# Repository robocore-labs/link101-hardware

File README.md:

# link101 Hardware

link101 is a multi-protocol USB interface board. One Type-C cable gives you CAN-FD, RS485, Dynamixel, Feetech, UART, I2C, and MIT Cheetah-protocol ports, all as stable Linux devices.

## Architecture

The LINK101 system consists of two boards:

- **link101** — The core module. RP2350-based controller in a 39.2×36.6mm form factor with 2× 1×15 pin headers.
- **link101_carrier** — The breakout carrier board. Exposes every bus as physical connectors, adds onboard sensors, neopixel indicators, and a 5V buck regulator.

## Boards

### link101 (Module)

The brains of the system. A Raspberry Pi RP2354A (dual Cortex-M33 at 150 MHz, 520 KB SRAM, 2 MB flash) with onboard peripherals:

| Feature | Detail |
|---|---|
| **USB** | USB Type-C composite device (CDC serial, SocketCAN, debug) |
| **CAN** | MCP2518FD CAN-FD controller + SN65HVD230 transceiver |
| **RS485** | SP3485EN half-duplex transceiver with DE control |
| **GPIO** | 7× GPIO, 4× ADC exposed via pin headers |
| **I2C** | Hardware I2C bus (SCL/SDA) |
| **SPI** | Hardware SPI (MOSI/MISO/SCK) |
| **UART** | 2× full-duplex UART (UART0, UART1) |
| **NeoPixel** | WS2812B-compatible output |
| **Power** | VBUS input, onboard 3.3V LDO (AP2112K-3.3), 1.1V core supply |
| **Protection** | ESD protection on CAN (PESD1CAN), USB (USBLC6-2SC6), and RS485 (PRTR5V0U2X) |
| **Debug** | SWD header, USB boot select |

**Files:** `link101.kicad_pro` (project), `link101.kicad_sch` (schematic), `link101.kicad_pcb` (layout), `link101_Module.kicad_sym` (symbol), `link101_Module.kicad_mod` (footprint)

### link101_carrier (Carrier Board)

Breaks out every signal from the module into real-world connectors, adds sensors, neopixel status LEDs, and power regulation:

| Section | Details |
|---|---|
| **Power** | XT30 input → LMR16006 5V buck regulator → SS54 reverse protection → servo power rail |
| **CAN-FD** | Screw terminals, MCP2518FD via module SPI |
| **RS485** | Screw terminals, hardware UART with DE pin |
| **UART0** | 5V-level full-duplex serial (XH2.54 connector) |
| **UART1** | 3.3V-level full-duplex serial (2.54mm pin header) |
| **Half-Duplex UART** | Feetech SCS/STS, Dynamixel Protocol 1.0/2.0, FashionStar bus servos (XH2.54 + Dynamixel connectors) |
| **I2C** | Qwiic/STEMMA QT connector (JST-GH 4-pin) |
| **SPI** | 2.54mm pin header |
| **MIT Cheetah** | XT30(2+2) connector for Damiao, CubeMars, Unitree, MyActuator |
| **ODrive** | JST-GH 4-pin connector |
| **IMU** | Onboard LSM6DSOX 6-axis IMU + MMC5983MA magnetometer via SPI |
| **NeoPixels** | WS2812B ×4 — one per bus (CAN, RS485, serial, servo) |
| **GPIO/ADC** | 7× GPIO + 4× ADC breakout pin headers |

**Files:** `link101_carrier.kicad_pro` (project), `link101_carrier.kicad_sch` (schematic), `link101_carrier.kicad_pcb` (layout)

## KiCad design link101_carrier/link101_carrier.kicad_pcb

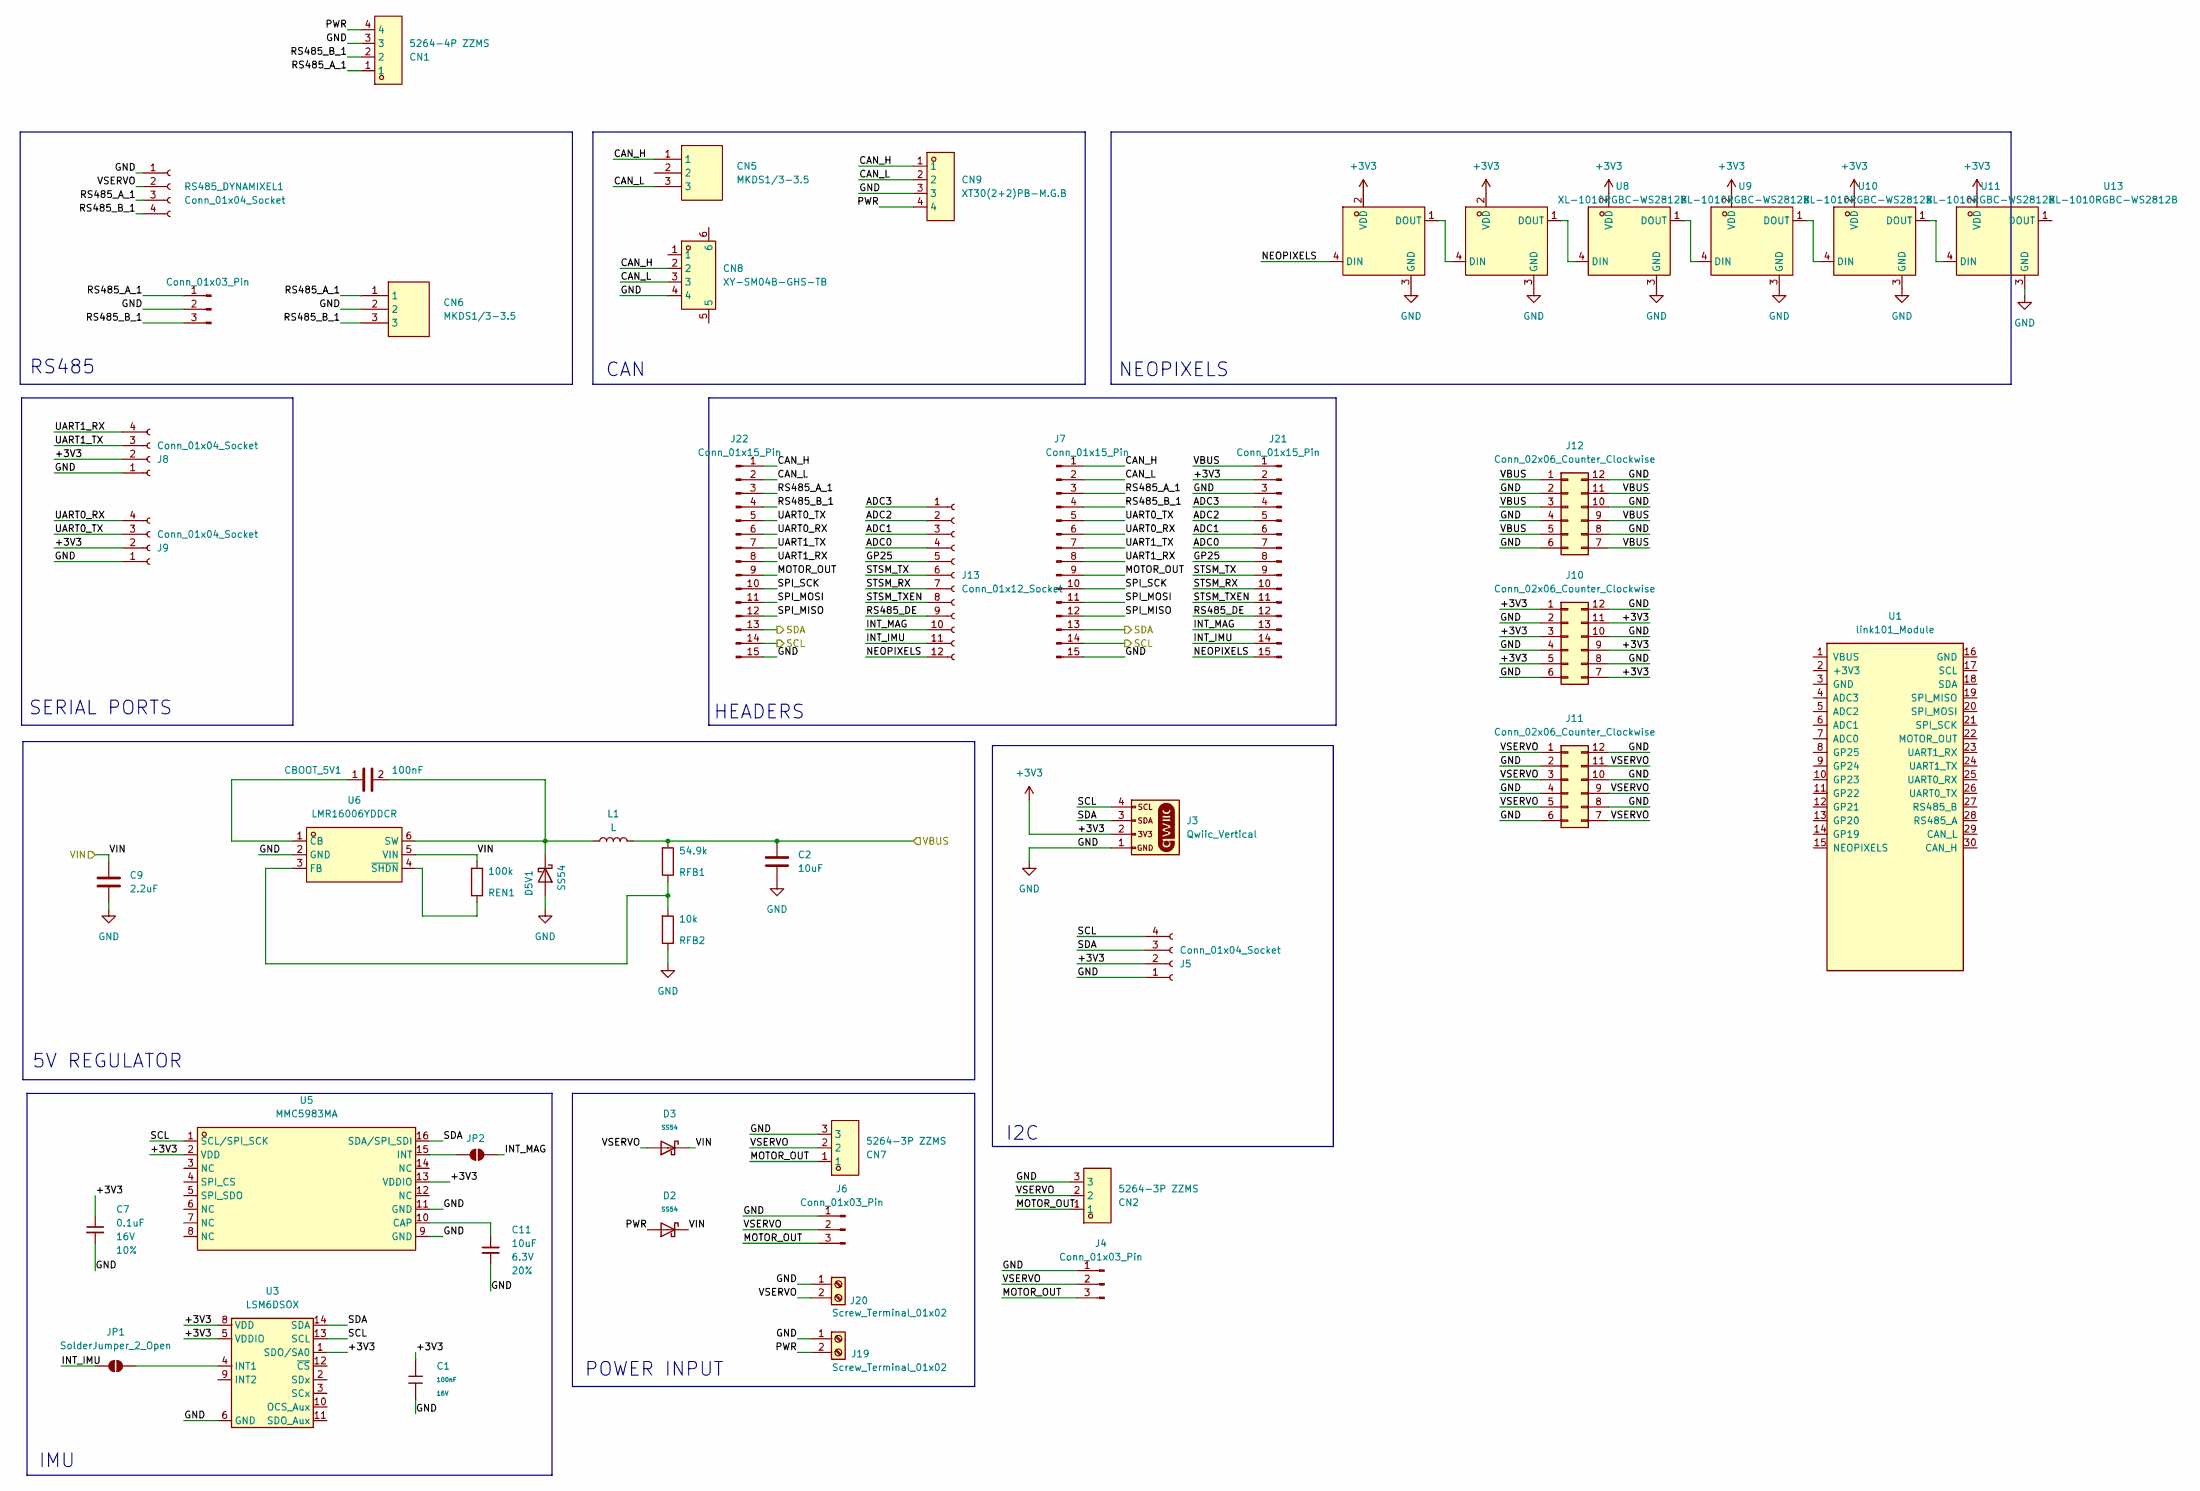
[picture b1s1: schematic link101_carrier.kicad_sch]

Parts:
C1: 100nF; C_0402; Voltage Rated 16V; Tolerance ±10%; Part CL05B104KO5NNNC; LCSC C1525
C2: 10uF; C_1206_3216Metric
C7: 0.1uF; C_0402_1005Metric; Voltage 16V; Tolerance 10%
C9: 2.2uF; C_1206_3216Metric
C11: 10uF; C_0402_1005Metric; Voltage 6.3V; Tolerance 20%
CBOOT_5V1: 100nF; C_0805_2012Metric
CN1: 5264-4P ZZMS; CONN-TH_4P-P2.50_5264-4P-ZZMS; LCSC Part C49023815
CN2, CN7: 5264-3P ZZMS; CONN-TH_5264-3P-ZZMS; LCSC Part C49023814
CN5, CN6: MKDS1/3-3.5; CONN-TH_3P-P3.50_1751251; LCSC Part C91152
CN8: XY-SM04B-GHS-TB; CONN-SMD_4P-P1.25_12502-04WASMT; LCSC Part C51940118
CN9: XT30(2+2)PB-M.G.B; CONN-TH_XT30PB-M; LCSC Part C19268029
D2, D3: SS54; D_2512_6332Metric; Forward Voltage (Vf@If) 550mV@5A; Reverse Voltage (Vr) 40V; Part SS54; LCSC C22452
D5V1: SS54; SMB_L4.3-W3.6-LS5.4-RD
J1: Conn_01x03_Pin; PinHeader_1x03_P2.54mm_Vertical
J3: Qwiic_Vertical; JST_1x04_P1.0mm_Vertical_SMD
J4, J6: Conn_01x03_Pin; JST_EH_B3B-EH-A_1x03_P2.50mm_Vertical
J5, J8, J9: Conn_01x04_Socket; JST_PH_B4B-PH-K_1x04_P2.00mm_Vertical
J7, J21, J22: Conn_01x15_Pin; PinSocket_1x15_P2.54mm_Vertical
J10, J11, J12: Conn_02x06_Counter_Clockwise; PinSocket_2x06_P2.54mm_Vertical
J13: Conn_01x12_Socket; PinSocket_1x12_P2.54mm_Vertical
J19, J20: Screw_Terminal_01x02; TerminalBlock_MetzConnect_Type094_RT03502HBLU_1x02_P5.00mm_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
JP1, JP2: SolderJumper_2_Open; SolderJumper-2_P1.3mm_Open_RoundedPad1.0x1.5mm
L1: L; L_Cenker_CKCS5040
REN1: 100k; R_0603_1608Metric
RFB1: 54.9k; R_0603_1608Metric
RFB2: 10k; R_0603_1608Metric
RS485_DYNAMIXEL1: Conn_01x04_Socket; JST_EH_B4B-EH-A_1x04_P2.50mm_Vertical
U1: link101_Module
U3: LSM6DSOX; ST_LGA-14L_2.5x3.0mm_P0.5mm_4x3
U5: MMC5983MA; LGA-16_L3.0-W3.0-P0.50-BL_SQ; LCSC Part C404329
U6: LMR16006YDDCR; SOT-23-6_L2.9-W1.6-P0.95-LS2.8-BL; MPN LMR16006YDDCR; LCSC Part C290195
U7, U8, U9, U10, U11, U13: XL-1010RGBC-WS2812B; LED-SMD_4P-L1.0-W1.0-TL_XL-1010RGBC-WS2812B; LCSC Part C5349953

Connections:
+3V3: C1.1, C7.1, J3.2, J5.2, J8.2, J9.2, J10.1, J10.3, J10.5, J10.7, J10.9, J10.11, J21.2, U3.1 (SDO/SA0), U3.5 (VDDIO), U3.8 (VDD), U5.2 (VDD), U5.13 (VDDIO), U7.2 (VDD), U8.2 (VDD), U9.2 (VDD), U10.2 (VDD), U11.2 (VDD), U13.2 (VDD)
/ADC0: J13.4, J21.7
/ADC1: J13.3, J21.6
/ADC2: J13.2, J21.5
/ADC3: J13.1, J21.4
/CAN_H: CN5.1, CN8.2, CN9.1, J7.1, J22.1
/CAN_L: CN5.3, CN8.3, CN9.2, J7.2, J22.2
/GP25: J13.5, J21.8
/INT_IMU: J13.11, J21.14, JP1.1 (A)
/INT_MAG: J13.10, J21.13, JP2.2 (B)
/MOTOR_OUT: CN2.1, CN7.1, J4.3, J6.3, J7.9, J22.9
/NEOPIXELS: J13.12, J21.15, U7.4 (DIN)
/PWR: CN1.4, CN9.4, D2.2, J19.2
/RS485_A_1: CN1.1, CN6.1, J1.1, J7.3, J22.3, RS485_DYNAMIXEL1.3
/RS485_B_1: CN1.2, CN6.3, J1.3, J7.4, J22.4, RS485_DYNAMIXEL1.4
/RS485_DE: J13.9, J21.12
/SCL: J3.4, J5.4, J7.14, J22.14, U3.13 (SCL), U5.1 (SCL/SPI_SCK)
/SDA: J3.3, J5.3, J7.13, J22.13, U3.14 (SDA), U5.16 (SDA/SPI_SDI)
/SPI_MISO: J7.12, J22.12
/SPI_MOSI: J7.11, J22.11
/SPI_SCK: J7.10, J22.10
/STSM_RX: J13.7, J21.10
/STSM_TX: J13.6, J21.9
/STSM_TXEN: J13.8, J21.11
/UART0_RX: J7.6, J9.4, J22.6
/UART0_TX: J7.5, J9.3, J22.5
/UART1_RX: J7.8, J8.4, J22.8
/UART1_TX: J7.7, J8.3, J22.7
/VBUS: C2.1, J12.1, J12.3, J12.5, J12.7, J12.9, J12.11, J21.1, L1.2, RFB1.2
/VIN: C9.1, D2.1, D3.1, REN1.2, U6.5 (VIN)
/VSERVO: CN2.2, CN7.2, D3.2, J4.2, J6.2, J11.1, J11.3, J11.5, J11.7, J11.9, J11.11, J20.2, RS485_DYNAMIXEL1.2
GND: C1.2, C2.2, C7.2, C9.2, C11.2, CN1.3, CN2.3, CN6.2, CN7.3, CN8.4, CN9.3, D5V1.2 (A), J1.2, J3.1, J4.1, J5.1, J6.1, J7.15, J8.1, J9.1, J10.2, J10.4, J10.6, J10.8, J10.10, J10.12, J11.2, J11.4, J11.6, J11.8, J11.10, J11.12, J12.2, J12.4, J12.6, J12.8, J12.10, J12.12, J19.1, J20.1, J21.3, J22.15, RFB2.1, RS485_DYNAMIXEL1.1, U3.6 (GND), U3.7 (GND), U5.9 (GND), U5.11 (GND), U6.2 (GND), U7.3 (GND), U8.3 (GND), U9.3 (GND), U10.3 (GND), U11.3 (GND), U13.3 (GND)
unnamed: CBOOT_5V1.2, D5V1.1 (K), L1.1, U6.6 (SW)
unnamed: JP1.2 (B), U3.4 (INT1)
unnamed: JP2.1 (A), U5.15 (INT)
unnamed: C11.1, U5.10 (CAP)
unnamed: CBOOT_5V1.1, U6.1 (CB)
unnamed: RFB1.1, RFB2.2, U6.3 (FB)
unnamed: REN1.1, U6.4 (~SHDN)
unnamed: U7.1 (DOUT), U8.4 (DIN)
unnamed: U8.1 (DOUT), U9.4 (DIN)
unnamed: U9.1 (DOUT), U10.4 (DIN)
unnamed: U10.1 (DOUT), U11.4 (DIN)
unnamed: U11.1 (DOUT), U13.4 (DIN)

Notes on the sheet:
HEADERS
I2C
IMU
5V REGULATOR
RS485
SERIAL PORTS
POWER INPUT
CAN
NEOPIXELS

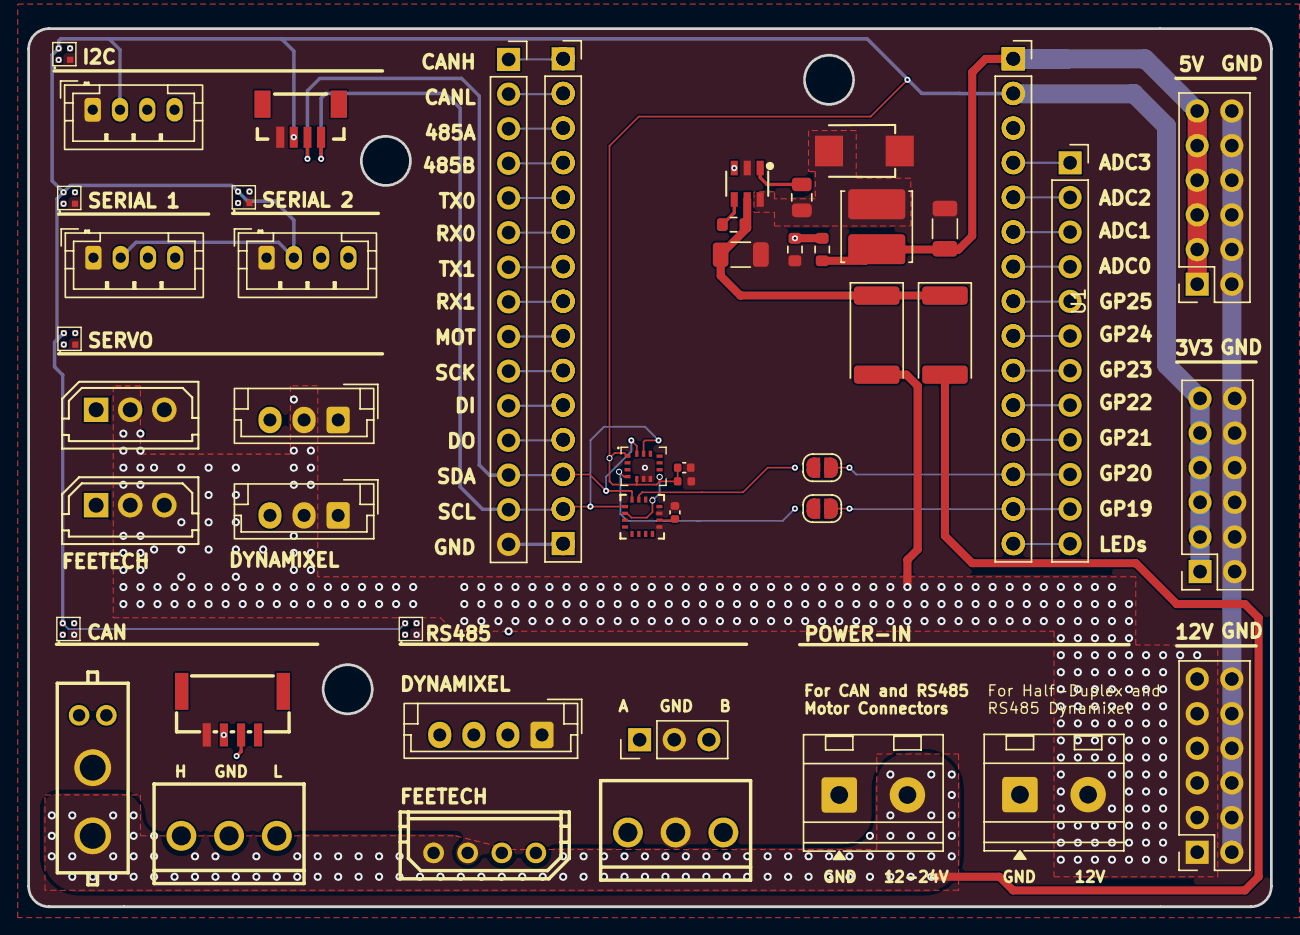
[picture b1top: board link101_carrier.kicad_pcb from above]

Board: 4 copper layers, 91.1 x 64.4 mm, 49 parts (0 on the bottom side), 44 nets.

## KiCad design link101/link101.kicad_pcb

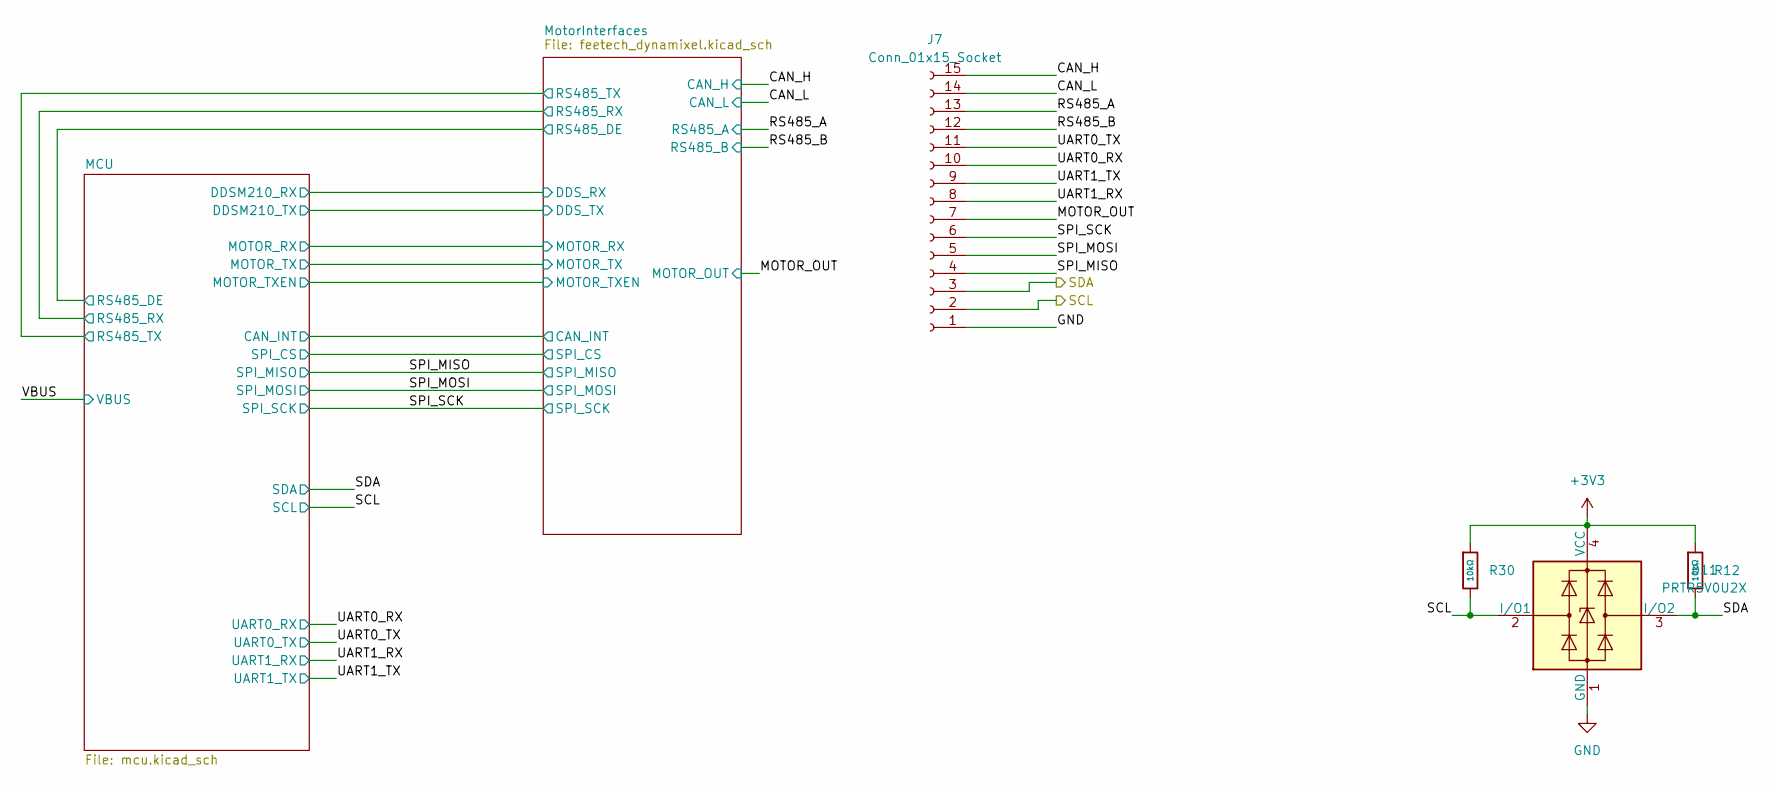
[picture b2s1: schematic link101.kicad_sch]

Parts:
D11: PRTR5V0U2X; SOT-143
J7: Conn_01x15_Socket; PinHeader_1x15_P2.54mm_Vertical
R12, R30: 10kΩ; R_0402; Overload Voltage (Max) 50V; Tolerance ±1%; Part 0402WGF1002TCE; LCSC C25744

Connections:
+3V3: D11.4 (VCC), R12.1, R30.1; also elsewhere on the board
/CAN_H: J7.15; also elsewhere on the board
/CAN_L: J7.14; also elsewhere on the board
/MOTOR_OUT: J7.7; also elsewhere on the board
/RS485_A: J7.13; also elsewhere on the board
/RS485_B: J7.12; also elsewhere on the board
/SCL: D11.2 (I/O1), J7.2, R30.2; also elsewhere on the board
/SDA: D11.3 (I/O2), J7.3, R12.2; also elsewhere on the board
/SPI_MISO: J7.4; also elsewhere on the board
/SPI_MOSI: J7.5; also elsewhere on the board
/SPI_SCK: J7.6; also elsewhere on the board
/UART0_RX: J7.10; also elsewhere on the board
/UART0_TX: J7.11; also elsewhere on the board
/UART1_RX: J7.8; also elsewhere on the board
/UART1_TX: J7.9; also elsewhere on the board
GND: D11.1 (GND), J7.1; also elsewhere on the board

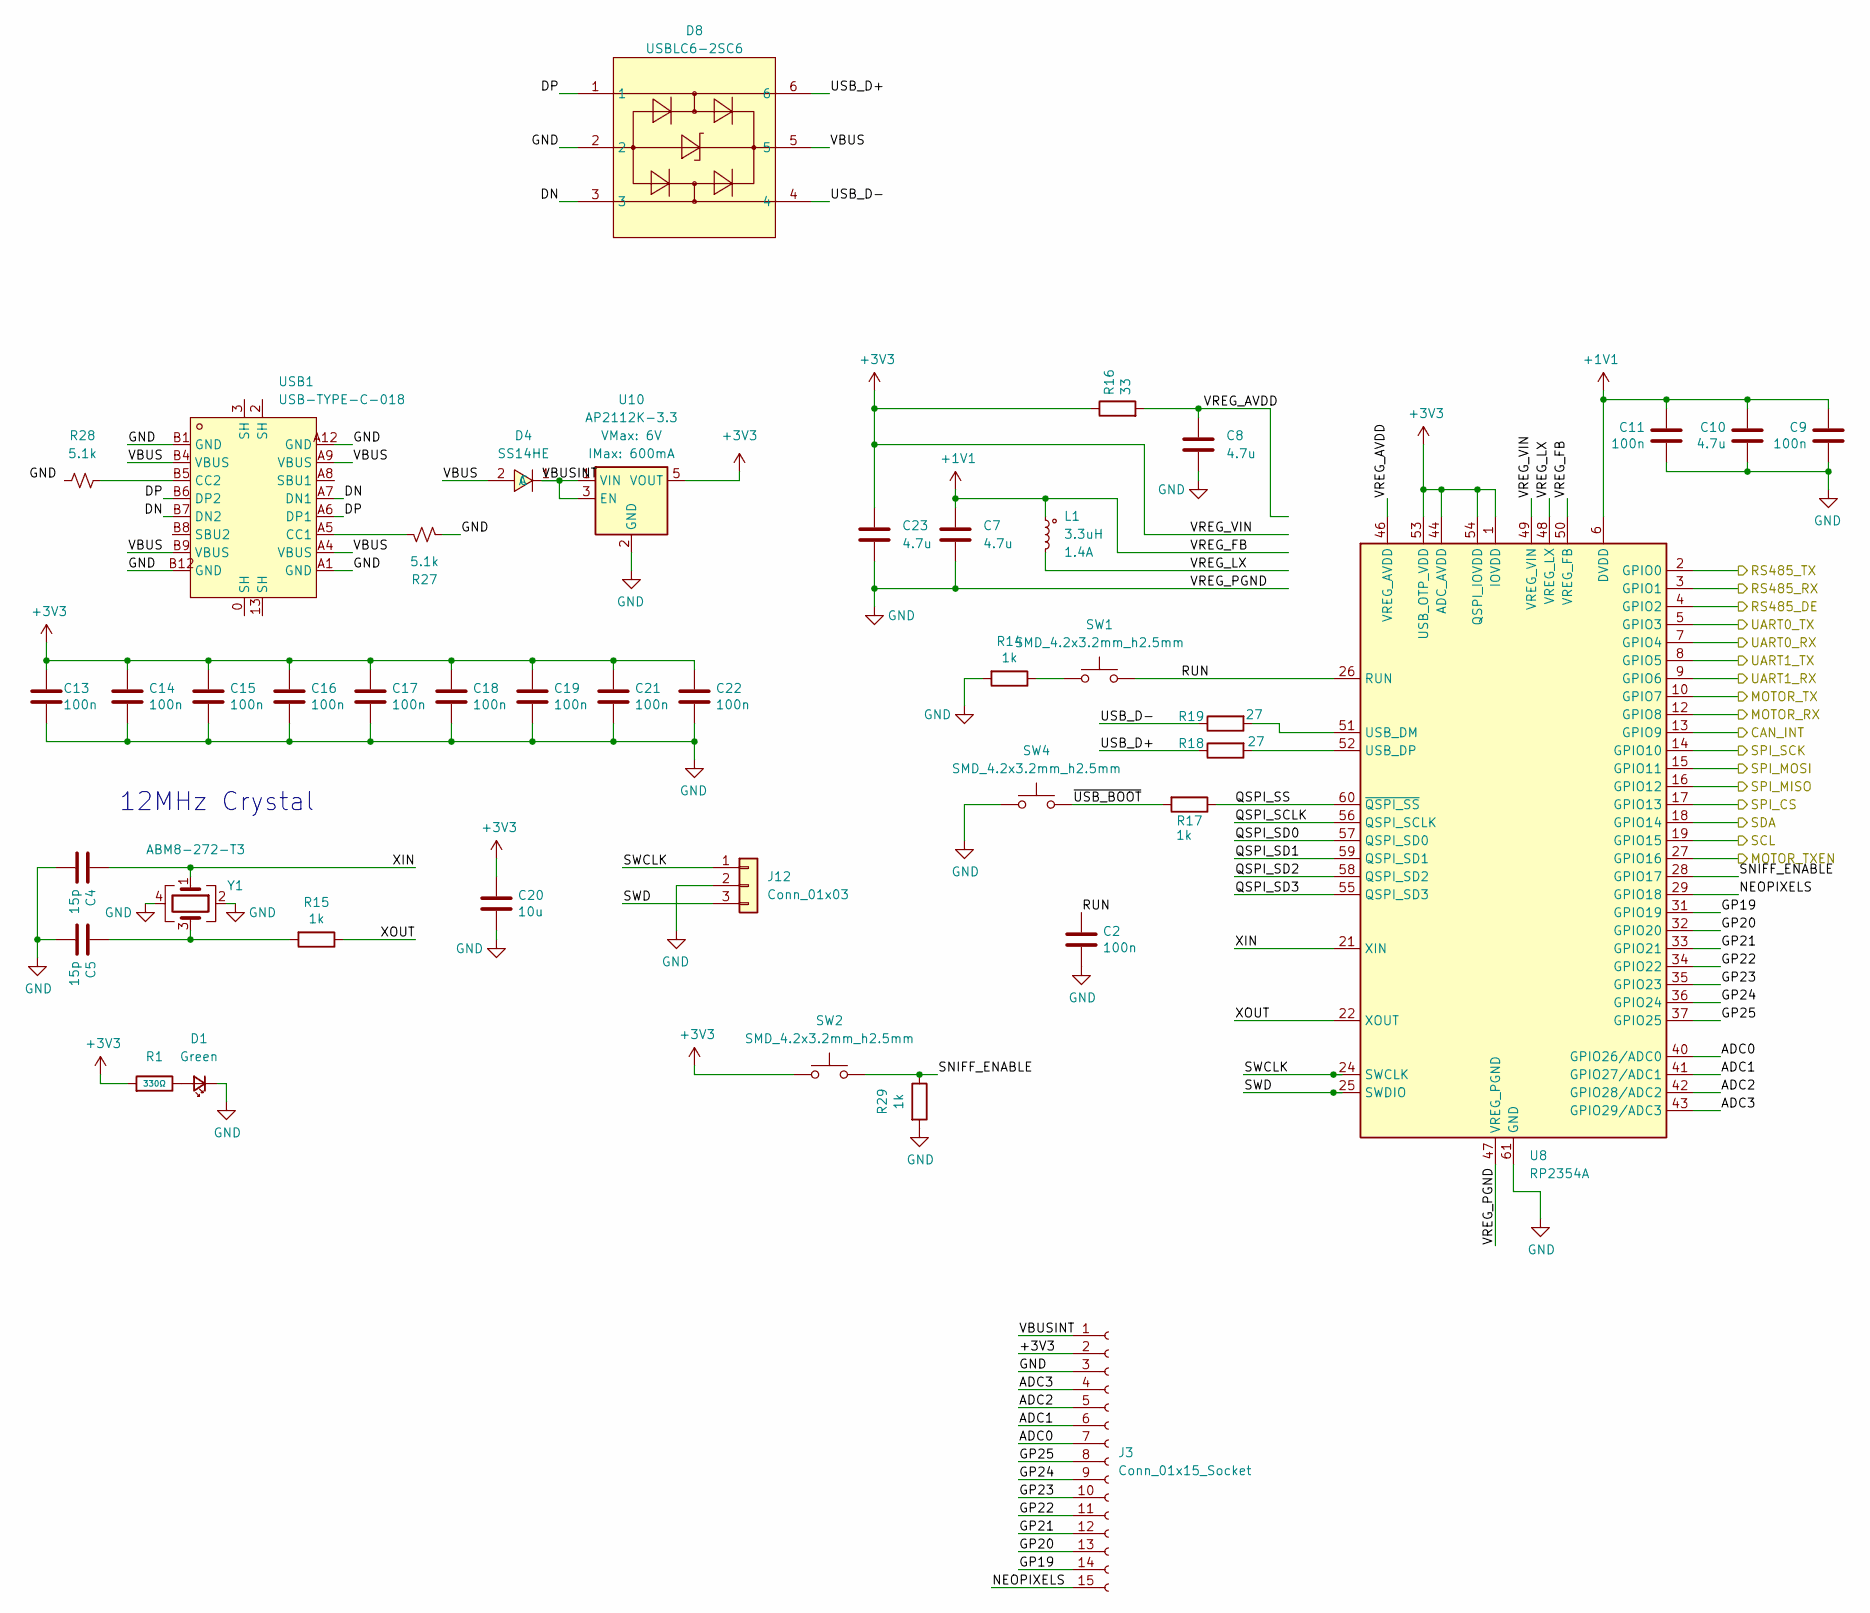
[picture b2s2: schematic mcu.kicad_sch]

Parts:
C2, C9, C11, C13, C14, C15, C16, C17, C18, C19, C21, C22: 100n; C_0402_1005Metric
C4, C5: 15p; C_0402_1005Metric
C7, C8, C10, C23: 4.7u; C_0402_1005Metric
C20: 10u; C_0805_2012Metric
D1: Green; LED_0603_1608Metric_Green
D4: SS14HE; SOD-323HE_L1.9-W1.3-LS2.5-RD; LCSC Part C28646397
D8: USBLC6-2SC6; SOT-23-6_L2.9-W1.6-P0.95-LS2.8-BL; LCSC Part C7519
J3: Conn_01x15_Socket; PinHeader_1x15_P2.54mm_Vertical
J12: Conn_01x03; 1x03_P2.54mm_Locking
L1: 3.3uH; 0806_Polarized
R1: 330Ω; R_0402; Overload Voltage (Max) 50V; Tolerance ±1%; Part 0402WGF3300TCE; LCSC C25104
R14, R15, R17, R29: 1k; R_0402_1005Metric
R16: 33; R_0402_1005Metric
R18, R19: 27; R_0402_1005Metric
R27, R28: 5.1k; R_0402_1005Metric
SW1, SW2, SW4: SMD_4.2x3.2mm_h2.5mm; Push_SMD_4.2x3.2mm
U8: RP2354A; QFN-60-1EP_7x7mm_P0.4mm_EP3.4x3.4mm
U10: AP2112K-3.3; SOT23-5
USB1: USB-TYPE-C-018; USB-C_SMD-TYPE-C-31-M-12; LCSC Part C2927038
Y1: ABM8-272-T3; Crystal_SMD_3225-4Pin_3.2x2.5mm

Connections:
+1V1: C7.1, C9.1, C10.1, C11.1, L1.1, U8.6 (DVDD), U8.23 (DVDD), U8.39 (DVDD), U8.50 (VREG_FB)
+3V3: C13.1, C14.1, C15.1, C16.1, C17.1, C18.1, C19.1, C20.1, C21.1, C22.1, C23.1, J3.2, R1.1, R16.1, SW2.1, U8.1 (IOVDD), U8.11 (IOVDD), U8.20 (IOVDD), U8.30 (IOVDD), U8.38 (IOVDD), U8.44 (ADC_AVDD), U8.45 (IOVDD), U8.49 (VREG_VIN), U8.53 (USB_OTP_VDD), U8.54 (QSPI_IOVDD), U10.5 (VOUT); also elsewhere on the board
/MCU/ADC0: J3.7, U8.40 (GPIO26/ADC0)
/MCU/ADC1: J3.6, U8.41 (GPIO27/ADC1)
/MCU/ADC2: J3.5, U8.42 (GPIO28/ADC2)
/MCU/ADC3: J3.4, U8.43 (GPIO29/ADC3)
/MCU/CAN_INT: U8.13 (GPIO9); also elsewhere on the board
/MCU/DN: D8.3, USB1.A7 (DN1), USB1.B7 (DN2)
/MCU/DP: D8.1, USB1.A6 (DP1), USB1.B6 (DP2)
/MCU/GP19: J3.14, U8.31 (GPIO19)
/MCU/GP20: J3.13, U8.32 (GPIO20)
/MCU/GP21: J3.12, U8.33 (GPIO21)
/MCU/GP22: J3.11, U8.34 (GPIO22)
/MCU/GP23: J3.10, U8.35 (GPIO23)
/MCU/GP24: J3.9, U8.36 (GPIO24)
/MCU/GP25: J3.8, U8.37 (GPIO25)
/MCU/NEOPIXELS: J3.15, U8.29 (GPIO18)
/MCU/QSPI_SCLK: U8.56 (QSPI_SCLK)
/MCU/QSPI_SD0: U8.57 (QSPI_SD0)
/MCU/QSPI_SD1: U8.59 (QSPI_SD1)
/MCU/QSPI_SD2: U8.58 (QSPI_SD2)
/MCU/QSPI_SD3: U8.55 (QSPI_SD3)
/MCU/QSPI_SS: R17.1, U8.60 (~QSPI_SS)
/MCU/RS485_DE: U8.4 (GPIO2); also elsewhere on the board
/MCU/RS485_RX: U8.3 (GPIO1); also elsewhere on the board
/MCU/RS485_TX: U8.2 (GPIO0); also elsewhere on the board
/MCU/RUN: C2.1, SW1.2, U8.26 (RUN)
/MCU/SNIFF_ENABLE: R29.1, SW2.2, U8.28 (GPIO17)
/MCU/SPI_CS: U8.17 (GPIO13); also elsewhere on the board
/MCU/SWCLK: J12.1, U8.24 (SWCLK)
/MCU/SWD: J12.3, U8.25 (SWDIO)
/MCU/USB_D+: D8.6, R18.1
/MCU/USB_D-: D8.4, R19.1
/MCU/VBUS: D4.2 (A), D8.5, USB1.A4 (VBUS), USB1.A9 (VBUS), USB1.B4 (VBUS), USB1.B9 (VBUS)
/MCU/VBUSINT: D4.1 (C), J3.1, U10.1 (VIN), U10.3 (EN)
/MCU/VREG_AVDD: C8.1, R16.2, U8.46 (VREG_AVDD)
/MCU/VREG_LX: L1.2, U8.48 (VREG_LX)
/MCU/XIN: C4.1, U8.21 (XIN), Y1.1
/MCU/XOUT: R15.1, U8.22 (XOUT)
/MCU/~USB_BOOT: R17.2, SW4.2
/MotorInterfaces/STSM_RX: U8.12 (GPIO8); also elsewhere on the board
/MotorInterfaces/STSM_TX: U8.10 (GPIO7); also elsewhere on the board
/MotorInterfaces/STSM_TXEN: U8.27 (GPIO16); also elsewhere on the board
/SCL: U8.19 (GPIO15); also elsewhere on the board
/SDA: U8.18 (GPIO14); also elsewhere on the board
/SPI_MISO: U8.16 (GPIO12); also elsewhere on the board
/SPI_MOSI: U8.15 (GPIO11); also elsewhere on the board
/SPI_SCK: U8.14 (GPIO10); also elsewhere on the board
/UART0_RX: U8.7 (GPIO4); also elsewhere on the board
/UART0_TX: U8.5 (GPIO3); also elsewhere on the board
/UART1_RX: U8.9 (GPIO6); also elsewhere on the board
/UART1_TX: U8.8 (GPIO5); also elsewhere on the board
GND: C2.2, C4.2, C5.2, C7.2, C8.2, C9.2, C10.2, C11.2, C13.2, C14.2, C15.2, C16.2, C17.2, C18.2, C19.2, C20.2, C21.2, C22.2, C23.2, D1.1 (K), D8.2, J3.3, J12.2, R14.2, R27.2, R29.2, SW4.1, U8.47 (VREG_PGND), U8.61 (GND), U10.2 (GND), USB1.A1 (GND), USB1.A12 (GND), USB1.B1 (GND), USB1.B12 (GND), Y1.2, Y1.4; also elsewhere on the board
unnamed: C5.1, R15.2, Y1.3
unnamed: D1.2 (A), R1.2
unnamed: R14.1, SW1.1
unnamed: R19.2, U8.51 (USB_DM)
unnamed: R18.2, U8.52 (USB_DP)
unnamed: R27.1, USB1.A5 (CC1)
unnamed: R28.2, USB1.B5 (CC2)

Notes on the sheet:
12MHz Crystal

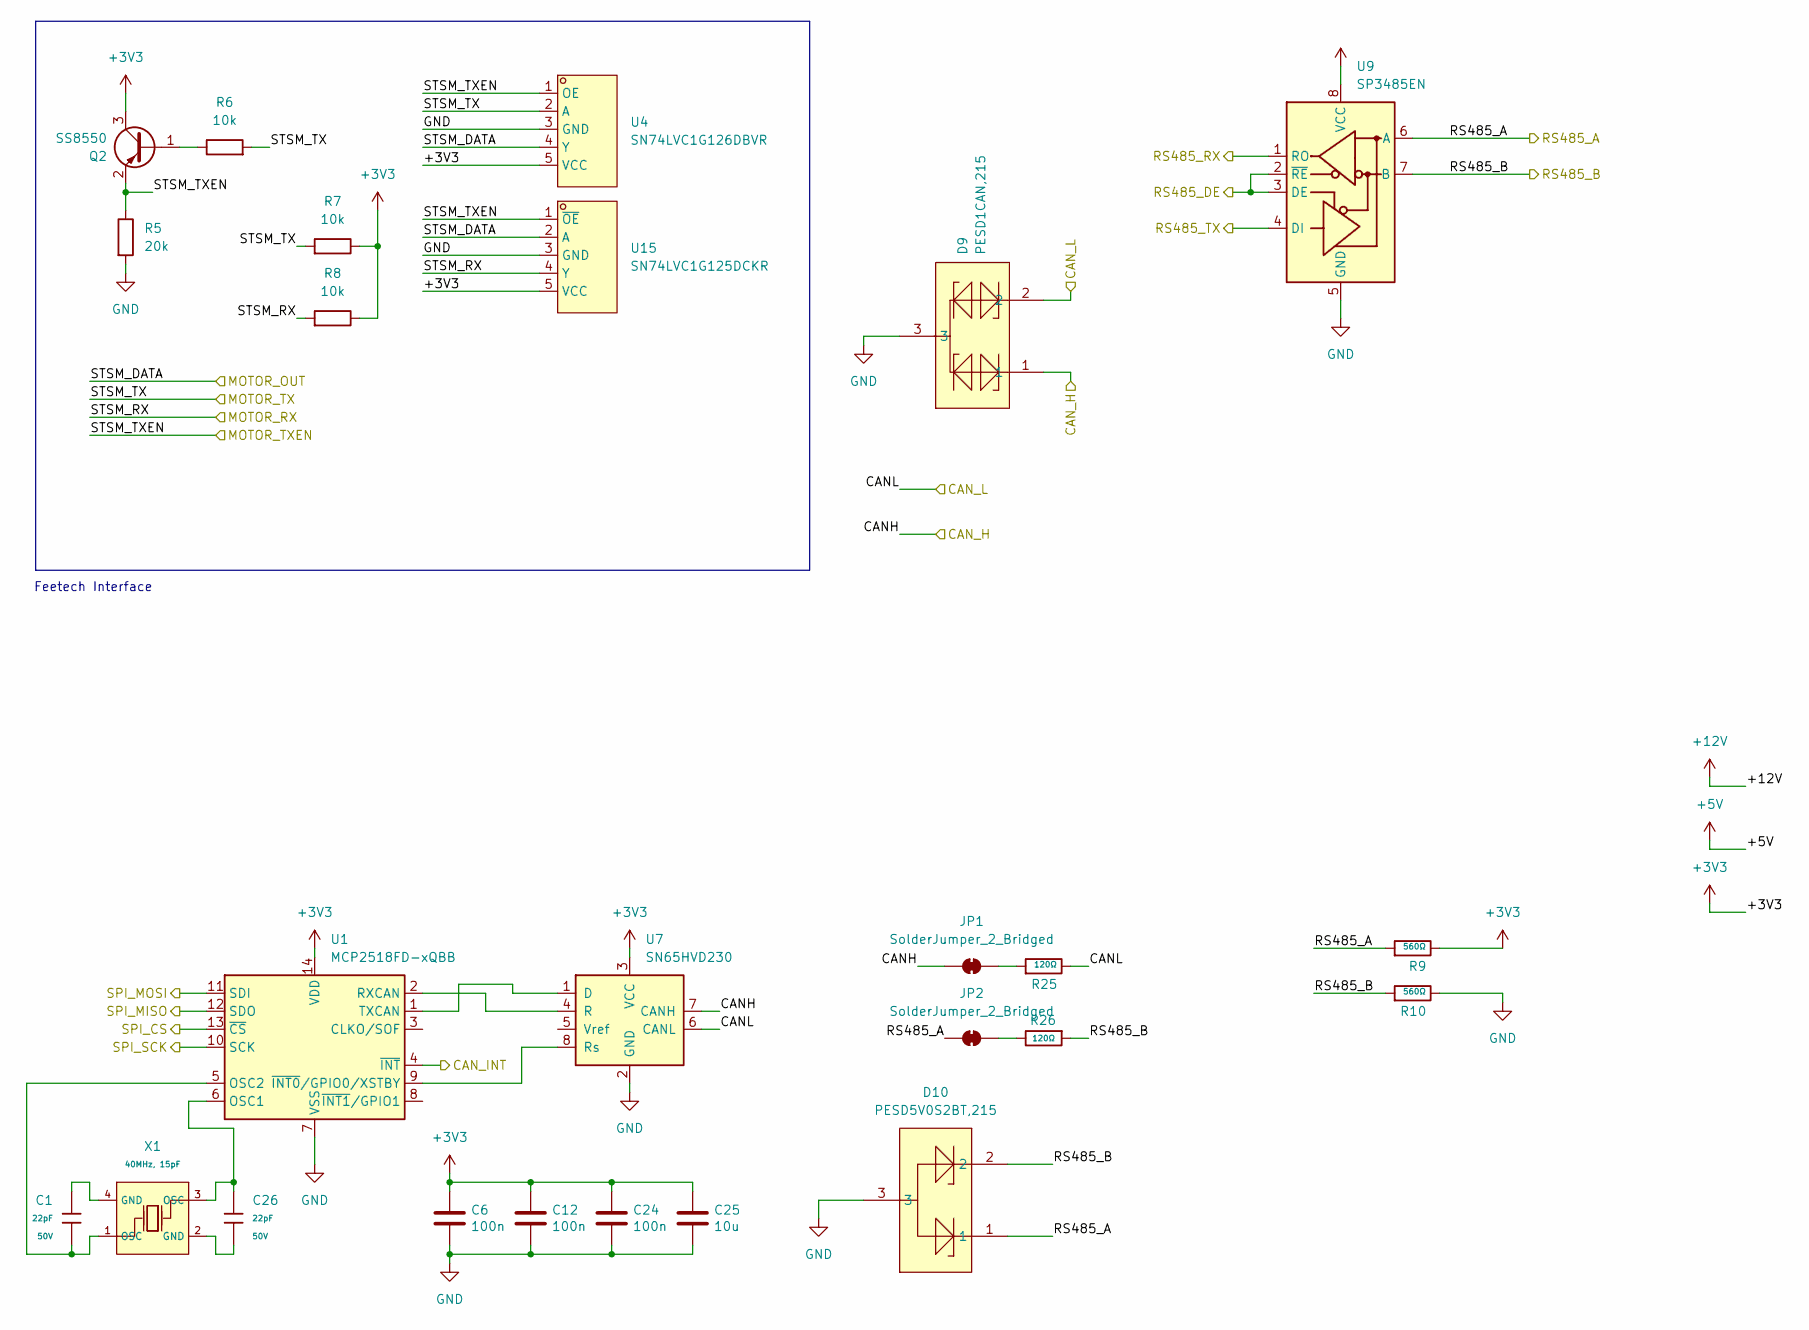
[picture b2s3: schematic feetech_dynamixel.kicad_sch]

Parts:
C1, C26: 22pF; C_0402; Voltage Rated 50V; Tolerance ±5%; Part 0402CG270J500NT; LCSC C1557
C6, C12, C24: 100n; C_0402_1005Metric
C25: 10u; C_0805_2012Metric
D9: PESD1CAN,215; SOT-23_L2.9-W1.3-P1.90-LS2.4-BR; LCSC Part C15771
D10: PESD5V0S2BT,215; SOT-23_L2.9-W1.3-P1.90-LS2.4-BR; LCSC Part C49338
JP1, JP2: SolderJumper_2_Bridged; SolderJumper-2_P1.3mm_Bridged_Pad1.0x1.5mm
Q2: SS8550; SOT-23
R5: 20k; R_0402_1005Metric
R6, R7, R8: 10k; R_0402_1005Metric
R9, R10: 560Ω; R_0402; Overload Voltage (Max) 50V; Tolerance ±1%; Part 0402WGF1200TCE; LCSC C25079
R25, R26: 120Ω; R_0402; Overload Voltage (Max) 50V; Tolerance ±1%; Part 0402WGF1200TCE; LCSC C25079
U1: MCP2518FD-xQBB; DFN-14-1EP_3x4.5mm_P0.65mm_EP1.65x4.25mm
U4: SN74LVC1G126DBVR; SOT-23-5_L3.0-W1.7-P0.95-LS2.8-BR; LCSC Part C7834
U7: SN65HVD230; SOIC-8_3.9x4.9mm_P1.27mm
U9: SP3485EN; SOIC-8_3.9x4.9mm_P1.27mm
U15: SN74LVC1G125DCKR; SOT-353_L2.2-W1.4-P0.65-LS2.4-BR; LCSC Part C7833
X1: 40MHz, 15pF; OSC-SMD_4P-L3.2-W2.5-BL_SIT8008BI; PartID X322540MPB4SI; LCSC C9010

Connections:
+3V3: C6.1, C12.1, C24.1, C25.1, Q2.3 (C), R7.1, R8.1, R9.2, U1.14 (VDD), U4.5 (VCC), U7.3 (VCC), U9.8 (VCC), U15.5 (VCC); also elsewhere on the board
/CAN_H: D9.1, JP1.1 (A), U7.7 (CANH); also elsewhere on the board
/CAN_L: D9.2, R25.2, U7.6 (CANL); also elsewhere on the board
/MCU/CAN_INT: U1.4 (~INT); also elsewhere on the board
/MCU/RS485_DE: U9.2 (~RE), U9.3 (DE); also elsewhere on the board
/MCU/RS485_RX: U9.1 (RO); also elsewhere on the board
/MCU/RS485_TX: U9.4 (DI); also elsewhere on the board
/MCU/SPI_CS: U1.13 (~CS); also elsewhere on the board
/MOTOR_OUT: U4.4 (Y), U15.2 (A); also elsewhere on the board
/MotorInterfaces/STSM_RX: R8.2, U15.4 (Y); also elsewhere on the board
/MotorInterfaces/STSM_TX: R6.2, R7.2, U4.2 (A); also elsewhere on the board
/MotorInterfaces/STSM_TXEN: Q2.2 (E), R5.1, U4.1 (OE), U15.1 (~OE); also elsewhere on the board
/RS485_A: D10.1, JP2.1 (A), R9.1, U9.6 (A); also elsewhere on the board
/RS485_B: D10.2, R10.1, R26.1, U9.7 (B); also elsewhere on the board
/SPI_MISO: U1.12 (SDO); also elsewhere on the board
/SPI_MOSI: U1.11 (SDI); also elsewhere on the board
/SPI_SCK: U1.10 (SCK); also elsewhere on the board
GND: C6.2, C12.2, C24.2, C25.2, D9.3, D10.3, R5.2, R10.2, U1.7 (VSS), U1.15 (VSS), U4.3 (GND), U7.2 (GND), U9.5 (GND), U15.3 (GND); also elsewhere on the board
unnamed: C1.1, X1.4 (GND)
unnamed: C26.2, X1.2 (GND)
unnamed: JP1.2 (B), R25.1
unnamed: JP2.2 (B), R26.2
unnamed: Q2.1 (B), R6.1
unnamed: C26.1, U1.6 (OSC1), X1.3 (OSC)
unnamed: C1.2, U1.5 (OSC2), X1.1 (OSC)
unnamed: U1.2 (RXCAN), U7.4 (R)
unnamed: U1.1 (TXCAN), U7.1 (D)
unnamed: U1.9 (~INT0/GPIO0/XSTBY), U7.8 (Rs)

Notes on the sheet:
Feetech Interface

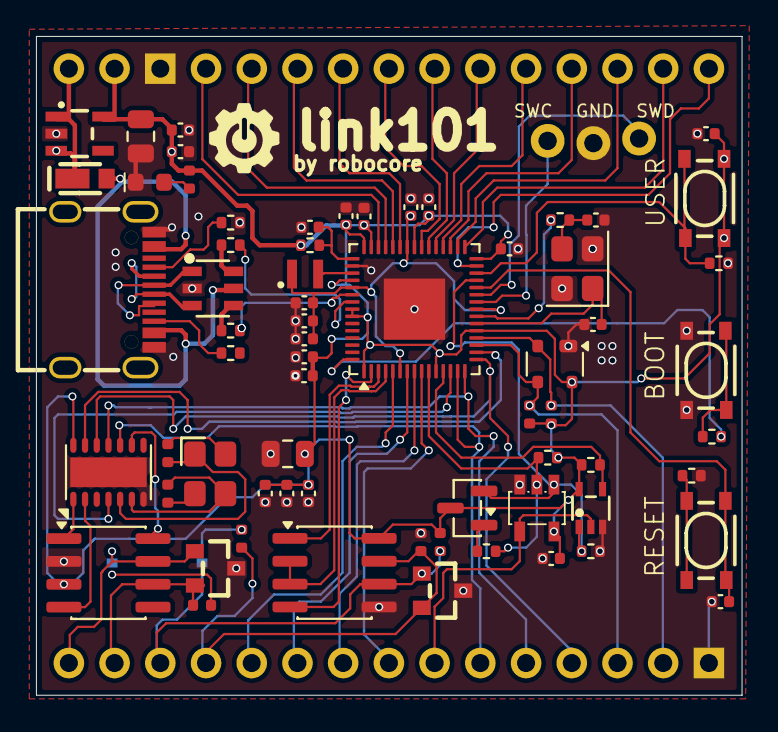
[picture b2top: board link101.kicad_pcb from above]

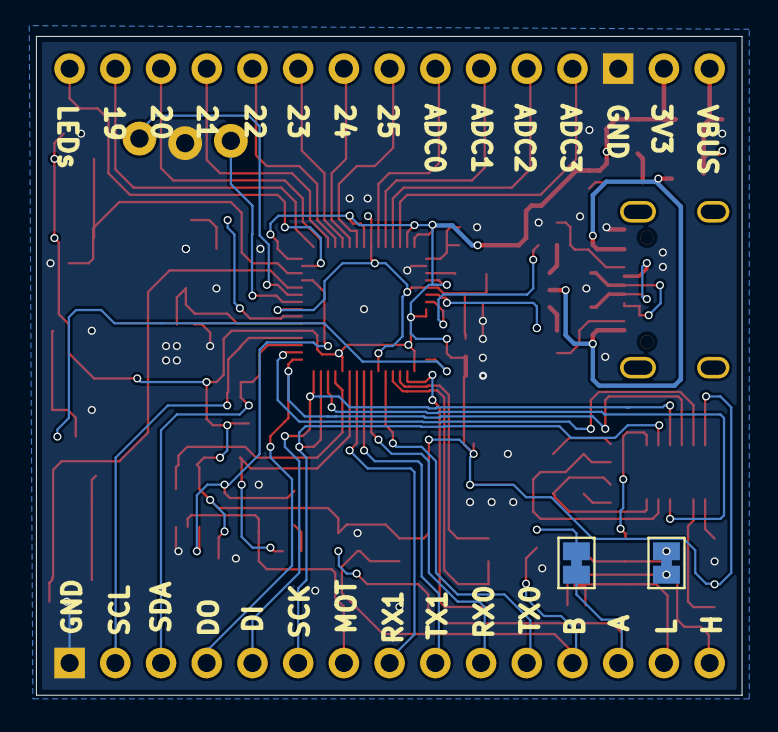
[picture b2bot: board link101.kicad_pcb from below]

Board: 2 copper layers, 39.2 x 36.6 mm, 71 parts (4 on the bottom side), 70 nets.
